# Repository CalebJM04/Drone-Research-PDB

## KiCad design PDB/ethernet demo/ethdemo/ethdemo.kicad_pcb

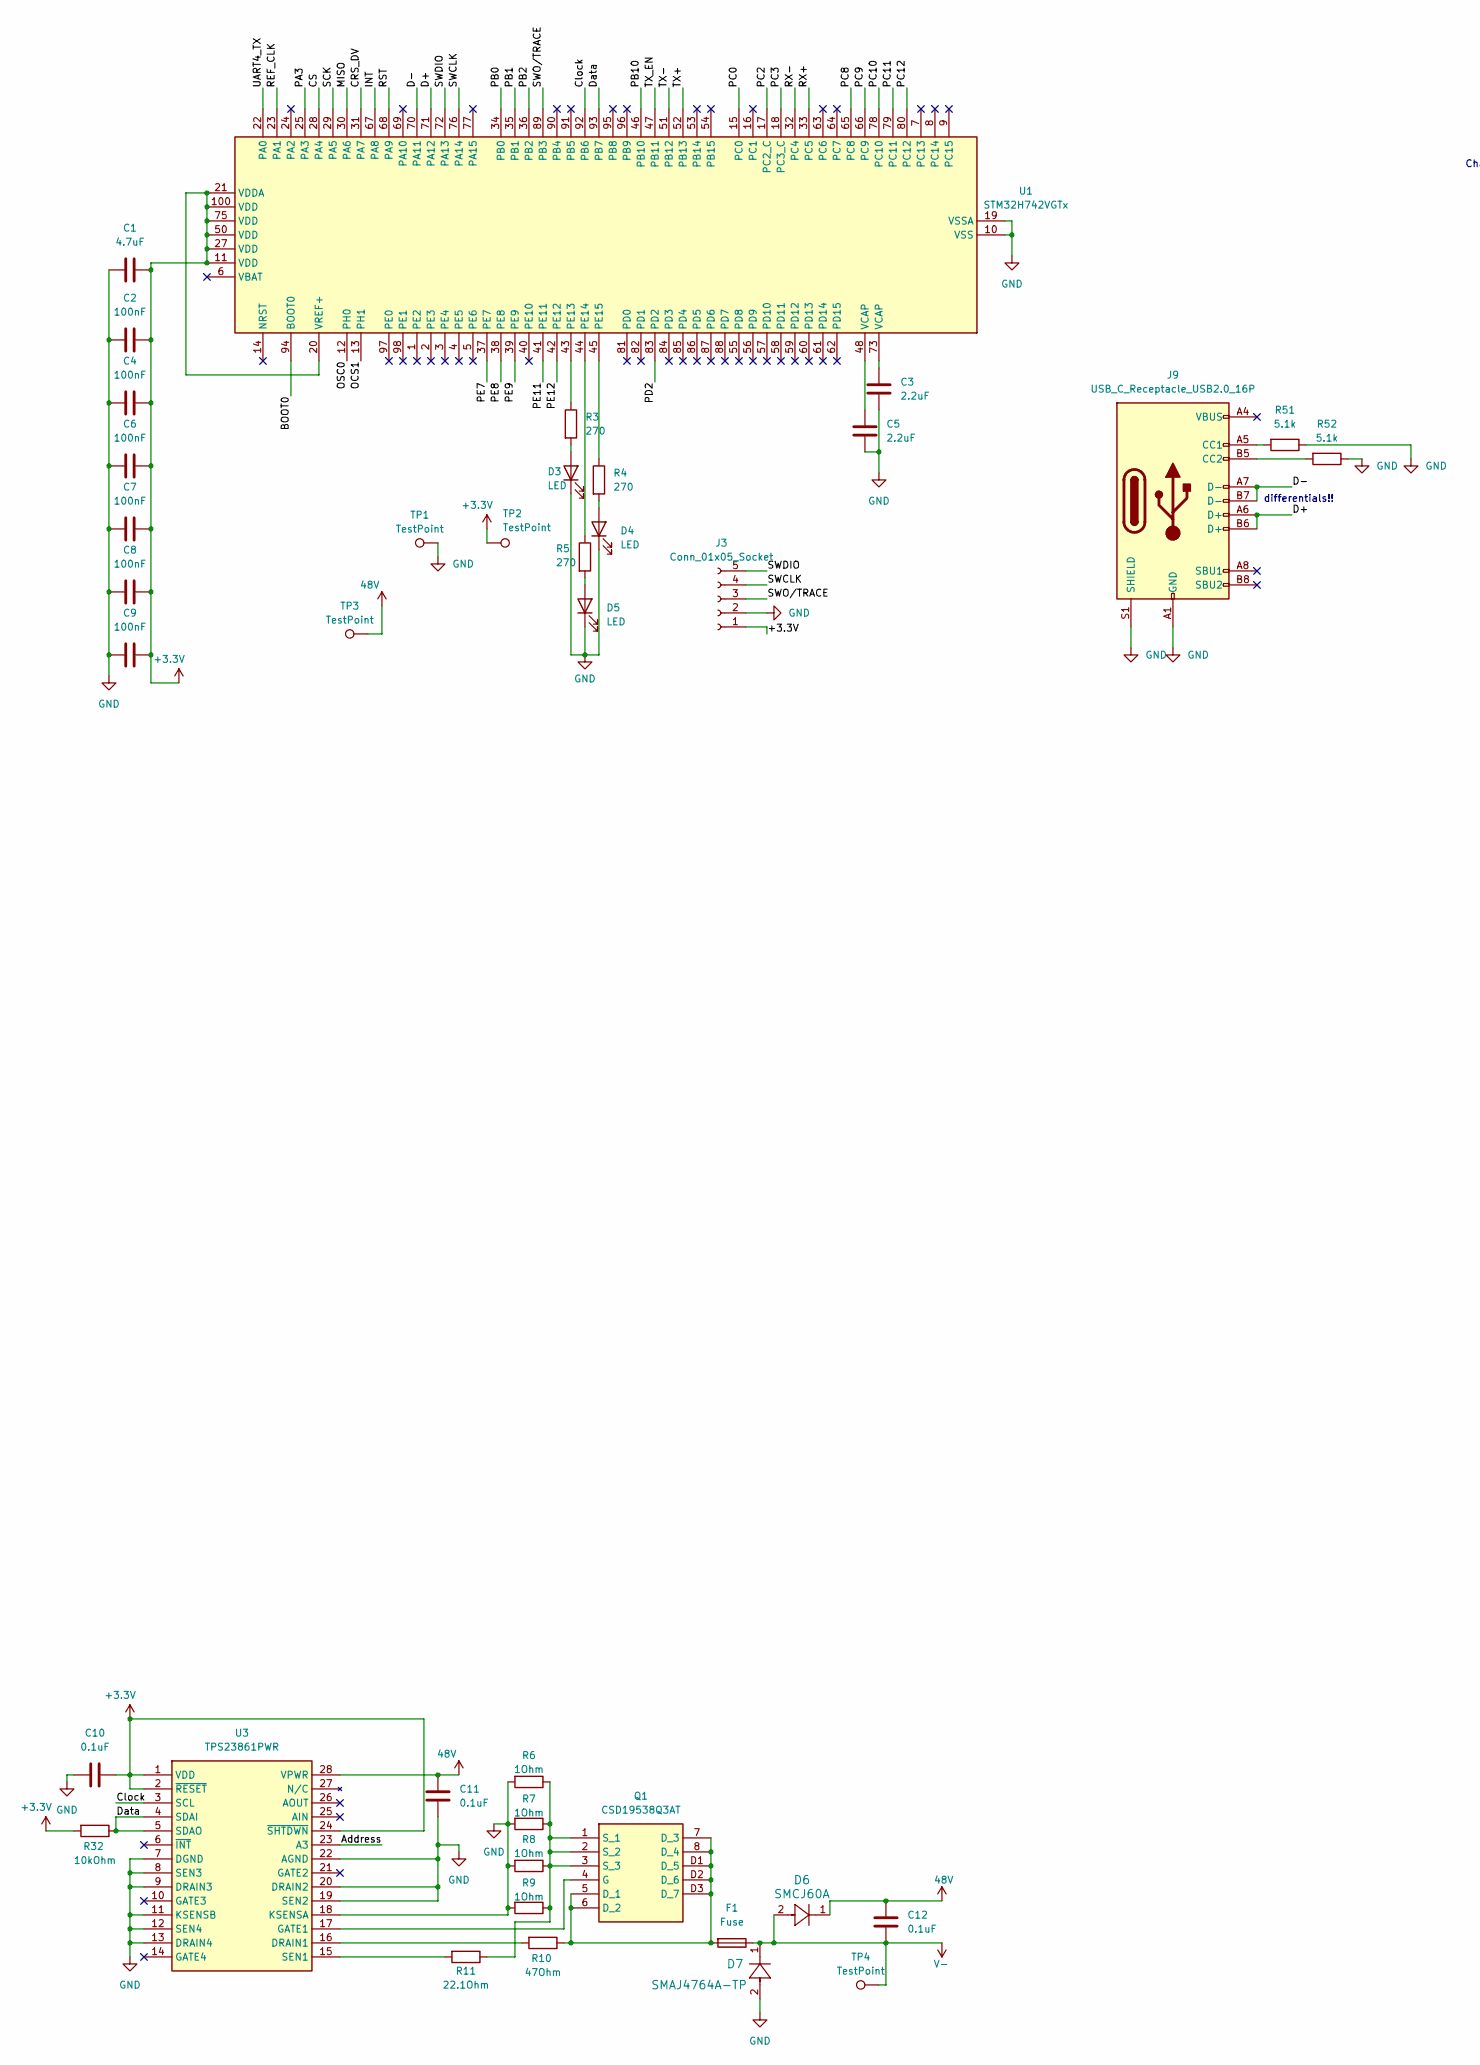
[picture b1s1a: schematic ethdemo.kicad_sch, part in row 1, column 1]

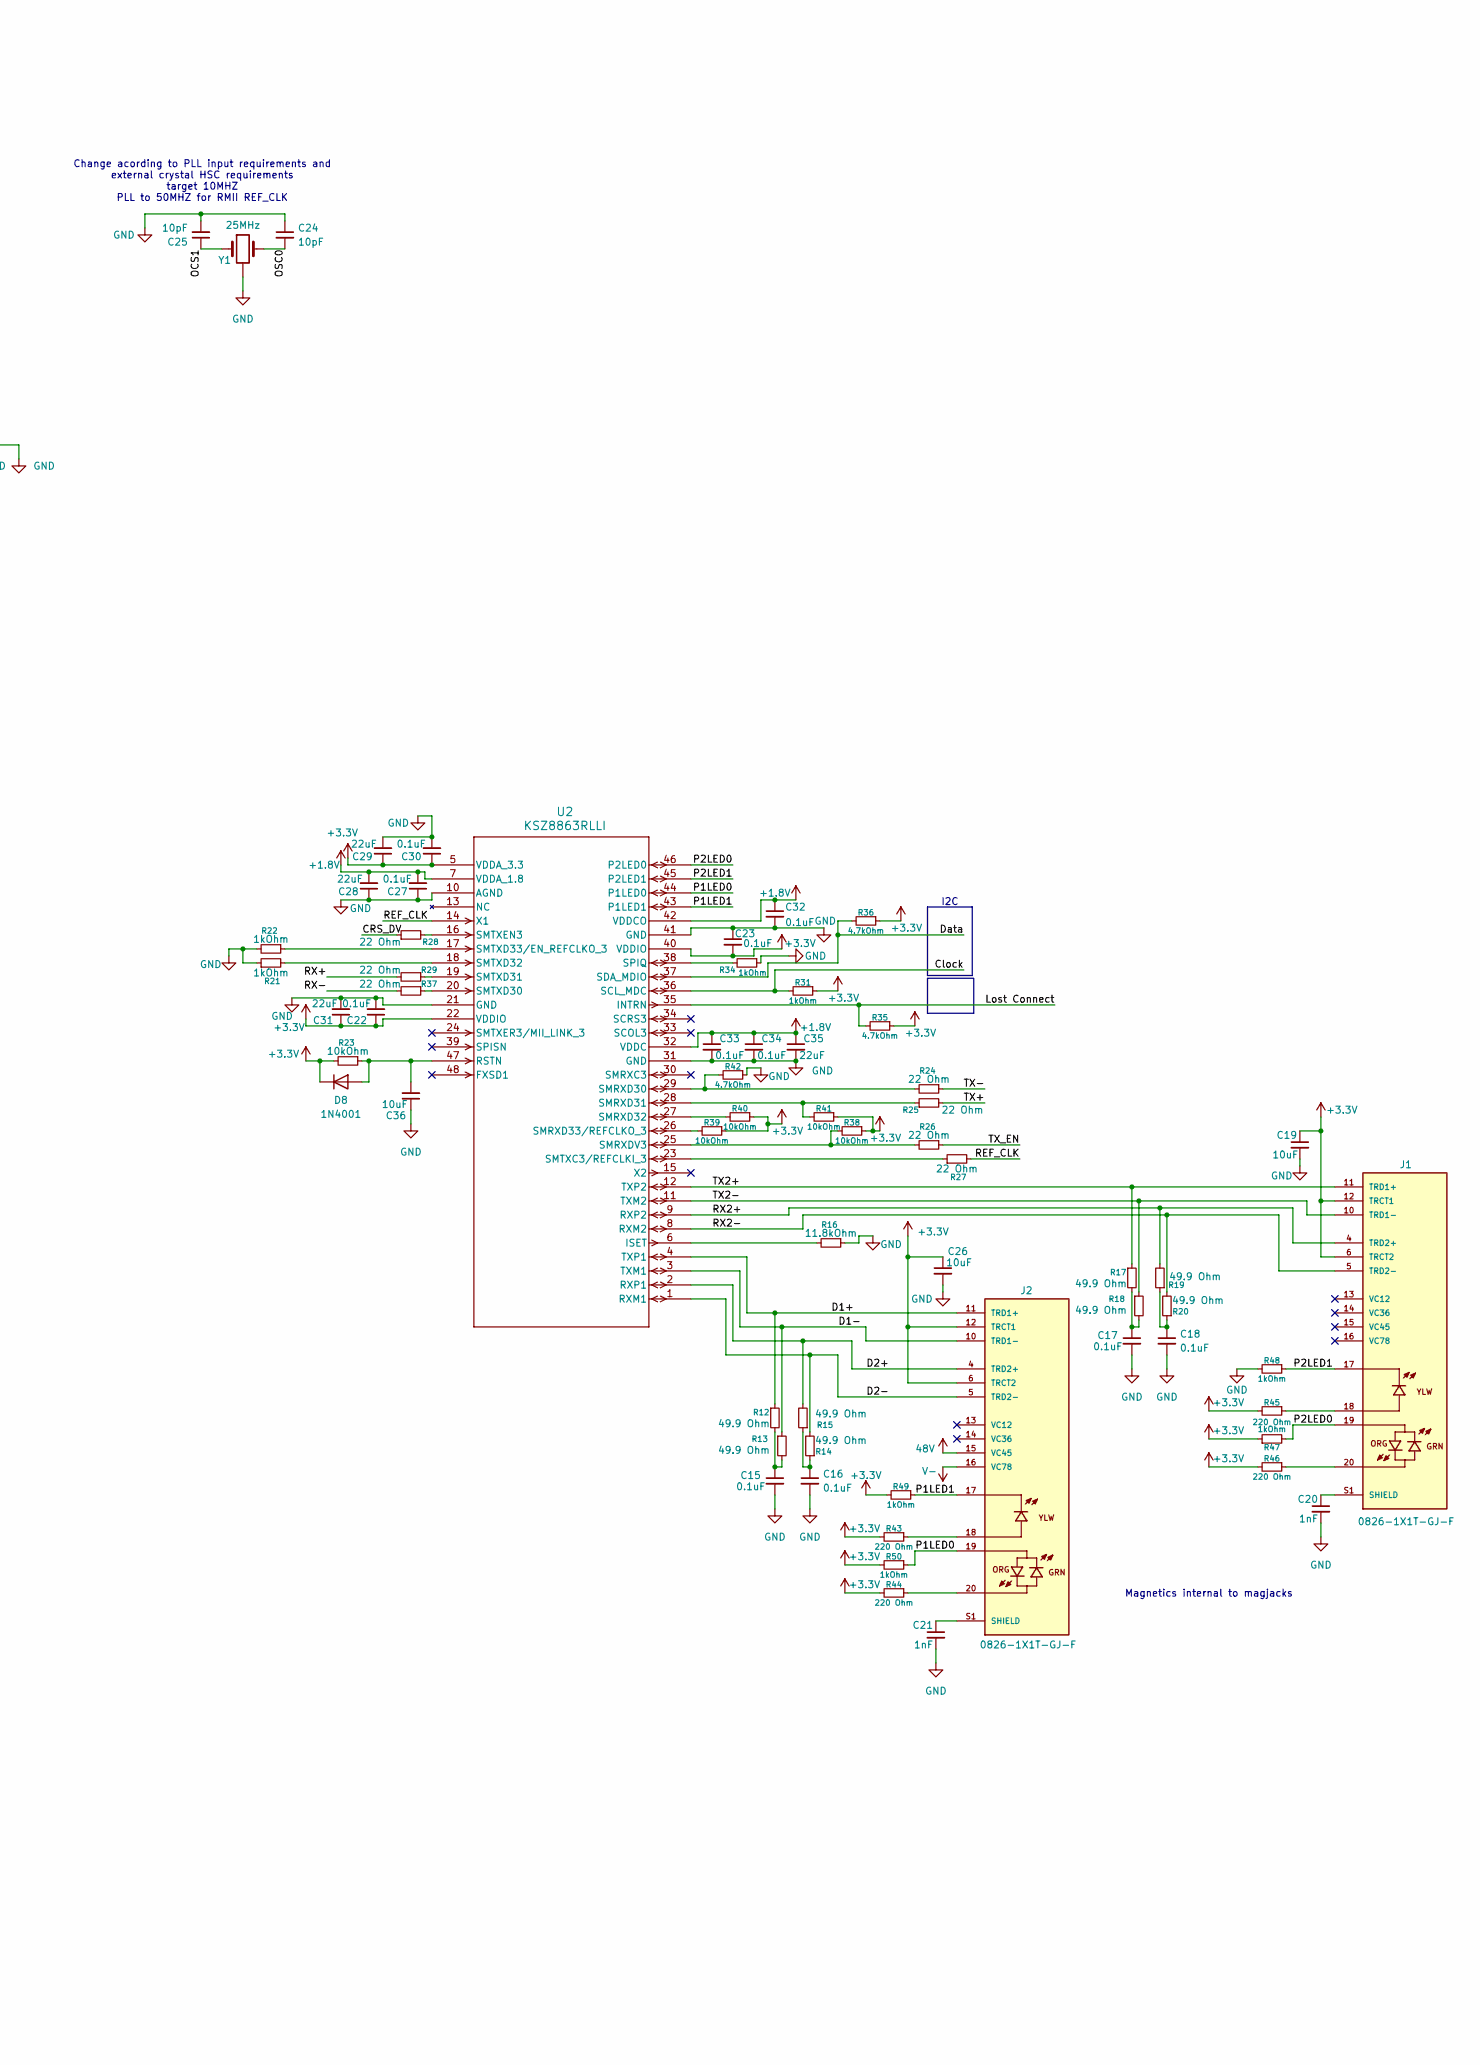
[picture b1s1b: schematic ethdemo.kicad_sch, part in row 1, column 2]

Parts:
C1: 4.7uF; C_0603_1608Metric
C2, C4, C6, C7, C8, C9: 100nF; C_0603_1608Metric
C3, C5: 2.2uF; C_0603_1608Metric
C10, C11, C12, C15, C16, C17, C18, C22, C23, C27, C30, C32, C33, C34: 0.1uF; C_0603_1608Metric
C19, C26, C36: 10uF; C_0603_1608Metric
C20, C21: 1nF; C_0603_1608Metric
C24, C25: 10pF; C_0603_1608Metric
C28, C29, C31, C35: 22uF; C_0603_1608Metric
D3, D4, D5: LED; LED_0805_2012Metric
D6: SMCJ60A
D7: SMAJ4764A-TP; SMAJ100CA_13_F
D8: 1N4001; D_SMA
F1: Fuse; Fuse_1206_3216Metric
J1, J2: 0826-1X1T-GJ-F; PARTREV D; DigiKey_Part_Number 5923-0826-1X1T-GJ-F-ND
J3: Conn_01x05_Socket; PinSocket_1x05_P2.54mm_Vertical
J9: USB_C_Receptacle_USB2.0_16P; USB_C_Receptacle_GCT_USB4105-xx-A_16P_TopMnt_Horizontal
Q1: CSD19538Q3AT; Mouser Part Number 595-CSD19538Q3AT
R3, R4, R5: 270; R_0603_1608Metric
R6, R7, R8, R9: 1Ohm; R_0603_1608Metric
R10: 47Ohm; R_0603_1608Metric
R11: 22.1Ohm; R_0603_1608Metric
R12, R13, R14, R15, R17, R18, R19, R20: 49.9 Ohm; R_0603_1608Metric
R16: 11.8kOhm; R_0603_1608Metric
R21, R22, R31, R34, R47, R48, R49, R50: 1kOhm; R_0603_1608Metric
R23, R32, R38, R39, R40, R41: 10kOhm; R_0603_1608Metric
R24, R25, R26, R27, R28, R29, R37: 22 Ohm; R_0603_1608Metric
R35, R36, R42: 4.7kOhm; R_0603_1608Metric
R43, R44, R45, R46: 220 Ohm; R_0603_1608Metric
R51, R52: 5.1k; R_0603_1608Metric_Pad0.98x0.95mm_HandSolder
TP1, TP2, TP3, TP4: TestPoint; TestPoint_Pad_D2.5mm
U1: STM32H742VGTx; LQFP-100_14x14mm_P0.5mm
U2: KSZ8863RLLI
U3: TPS23861PWR; Mouser Part Number 595-TPS23861PWR
Y1: 25MHz; Crystal_SMD_5032-4Pin_5.0x3.2mm

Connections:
48V: C11.2, C12.1, D6.1, J2.15 (VC45), TP3.1 (1_1), U3.28 (VPWR)
+1.8V: C27.2, C28.2, C32.1, C33.1, C34.1, C35.1, U2.7 (VDDA_1.8), U2.32 (VDDC), U2.42 (VDDCO)
+3.3V: C1.1, C2.1, C4.2, C6.1, C7.1, C8.1, C9.1, C10.1, C19.1, C22.1, C23.2, C26.1, C29.1, C30.1, C31.1, D8.1 (K), J1.6 (TRCT2), J1.12 (TRCT1), J2.6 (TRCT2), J2.12 (TRCT1), J3.1, R23.2, R31.1, R32.2, R35.1, R36.1, R38.1, R39.1, R40.1, R41.1, R43.2, R44.2, R45.2, R46.2, R47.1, R49.2, R50.2, TP2.1 (1_1), U1.11 (VDD), U1.20 (VREF+), U1.21 (VDDA), U1.27 (VDD), U1.50 (VDD), U1.75 (VDD), U1.100 (VDD), U2.5 (VDDA_3.3), U2.22 (VDDIO), U2.40 (VDDIO), U3.1 (VDD), U3.2 (~RESET), U3.24 (~SHTDWN)
/Address: U3.23 (A3)
/BOOT0: U1.94 (BOOT0)
/CRS_DV: R28.1, U1.31 (PA7)
/CS: U1.28 (PA4)
/Clock: R31.2, U1.92 (PB6), U2.36 (SCL_MDC), U3.3 (SCL)
/D1+: J2.11 (TRD1+), R12.1, U2.4 (TXP1)
/D1-: J2.10 (TRD1-), R13.1, U2.3 (TXM1)
/D2+: J2.4 (TRD2+), R15.2, U2.2 (RXP1)
/D2-: J2.5 (TRD2-), R14.2, U2.1 (RXM1)
/D+: J9.A6 (D+), J9.B6 (D+), U1.71 (PA12)
/D-: J9.A7 (D-), J9.B7 (D-), U1.70 (PA11)
/Data: R32.1, R36.2, U1.93 (PB7), U2.37 (SDA_MDIO), U3.4 (SDAI), U3.5 (SDAO)
/INT: U1.67 (PA8)
/Lost Connect: R35.2, U2.35 (INTRN)
/MISO: U1.30 (PA6)
/OCS1: C25.1, U1.13 (PH1), Y1.1
/OSC0: C24.2, U1.12 (PH0), Y1.3 (2)
/P1LED0: J2.19, R50.1, U2.44 (P1LED0)
/P1LED1: J2.17, R49.1, U2.43 (P1LED1)
/P2LED0: J1.19, R47.2, U2.46 (P2LED0)
/P2LED1: J1.17, R48.1, U2.45 (P2LED1)
/PA3: U1.25 (PA3)
/PB0: U1.34 (PB0)
/PB1: U1.35 (PB1)
/PB2: U1.36 (PB2)
/PB10: U1.46 (PB10)
/PC0: U1.15 (PC0)
/PC2: U1.17 (PC2_C)
/PC3: U1.18 (PC3_C)
/PC8: U1.65 (PC8)
/PC9: U1.66 (PC9)
/PC10: U1.78 (PC10)
/PC11: U1.79 (PC11)
/PC12: U1.80 (PC12)
/PD2: U1.83 (PD2)
/PE7: U1.37 (PE7)
/PE8: U1.38 (PE8)
/PE9: U1.39 (PE9)
/PE11: U1.41 (PE11)
/PE12: U1.42 (PE12)
/REF_CLK: R27.2, U1.23 (PA1), U2.14 (X1)
/RST: U1.68 (PA9)
/RX2+: J1.4 (TRD2+), R19.2, U2.9 (RXP2)
/RX2-: J1.5 (TRD2-), R20.2, U2.8 (RXM2)
/RX+: R29.2, U1.33 (PC5)
/RX-: R37.2, U1.32 (PC4)
/SCK: U1.29 (PA5)
/SWCLK: J3.4, U1.76 (PA14)
/SWDIO: J3.5, U1.72 (PA13)
/SWO/TRACE: J3.3, U1.89 (PB3)
/TX2+: J1.11 (TRD1+), R17.1, U2.12 (TXP2)
/TX2-: J1.10 (TRD1-), R18.1, U2.11 (TXM2)
/TX+: R25.2, U1.52 (PB13)
/TX-: R24.1, U1.51 (PB12)
/TX_EN: R26.1, U1.47 (PB11)
/UART4_TX: U1.22 (PA0)
GND: C1.2, C2.2, C3.1, C4.1, C5.1, C6.2, C7.2, C8.2, C9.2, C10.2, C11.1, C15.2, C16.2, C17.2, C18.2, C19.2, C20.2, C21.2, C22.2, C23.1, C24.1, C25.2, C26.2, C27.1, C28.1, C29.2, C30.2, C31.2, C32.2, C33.2, C34.2, C35.2, C36.1, D3.1 (K), D4.1 (K), D5.1 (K), D7.2, J3.2, J9.A1 (GND), J9.A12 (GND), J9.B1 (GND), J9.B12 (GND), J9.S1 (SHIELD), R6.2, R7.2, R8.2, R9.2, R16.1, R21.1, R22.2, R34.1, R42.1, R48.2, R51.1, R52.1, TP1.1 (1_1), U1.10 (VSS), U1.19 (VSSA), U1.26 (VSS), U1.49 (VSS), U1.74 (VSS), U1.99 (VSS), U2.10 (AGND), U2.21 (GND), U2.31 (GND), U2.41 (GND), U3.7 (DGND), U3.8 (SEN3), U3.9 (DRAIN3), U3.11 (KSENSB), U3.12 (SEN4), U3.13 (DRAIN4), U3.18 (KSENSA), U3.19 (SEN2), U3.20 (DRAIN2), U3.22 (AGND), Y1.2 (GND)
unnamed: C3.2, U1.73 (VCAP)
unnamed: C5.2, U1.48 (VCAP)
unnamed: C15.1, R12.2, R13.2
unnamed: C16.1, R14.1, R15.1
unnamed: C17.1, R17.2, R18.2
unnamed: C18.1, R19.1, R20.1
unnamed: C20.1, J1.S1 (SHIELD), J1.S2 (SHIELD)
unnamed: C21.1, J2.S1 (SHIELD), J2.S2 (SHIELD)
unnamed: D3.2 (A), R3.2
unnamed: D4.2 (A), R4.2
unnamed: D5.2 (A), R5.2
unnamed: C36.2, D8.2 (A), R23.1, U2.47 (RSTN)
unnamed: J1.18, R45.1
unnamed: J1.20, R46.1
unnamed: J2.18, R43.1
unnamed: J2.20, R44.1
unnamed: J9.A5 (CC1), R51.2
unnamed: J9.B5 (CC2), R52.2
unnamed: F1.2, Q1.5 (D_1), Q1.6 (D_2), Q1.7 (D_3), Q1.8 (D_4), Q1.D1 (D_5), Q1.D2 (D_6), Q1.D3 (D_7), R10.1
unnamed: Q1.4 (G), U3.17 (GATE1)
unnamed: Q1.1 (S_1), Q1.2 (S_2), Q1.3 (S_3), R6.1, R7.1, R8.1, R9.1, R11.1
unnamed: R3.1, U1.43 (PE13)
unnamed: R5.1, U1.44 (PE14)
unnamed: R4.1, U1.45 (PE15)
unnamed: R16.2, U2.6 (ISET)
unnamed: R24.2, R42.2, U2.29 (SMRXD30)
unnamed: R25.1, R41.2, U2.28 (SMRXD31)
unnamed: R40.2, U2.27 (SMRXD32)
unnamed: R39.2, U2.26 (SMRXD33/REFCLKO_3)
unnamed: R26.2, R38.2, U2.25 (SMRXDV3)
unnamed: R27.1, U2.23 (SMTXC3/REFCLKI_3)
unnamed: R37.1, U2.20 (SMTXD30)
unnamed: R29.1, U2.19 (SMTXD31)
unnamed: R21.2, U2.18 (SMTXD32)
unnamed: R22.1, U2.17 (SMTXD33/EN_REFCLKO_3)
unnamed: R28.2, U2.16 (SMTXEN3)
unnamed: R34.2, U2.38 (SPIQ)
unnamed: R10.2, U3.16 (DRAIN1)
unnamed: R11.2, U3.15 (SEN1)
V-: C12.2, D6.2, D7.1, F1.1, J2.16 (VC78), TP4.1 (1_1)

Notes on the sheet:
Magnetics internal to magjacks
differentials!!
I2C
Change acording to PLL input requirements and external crystal HSC requirements target 10MHZ PLL to 50MHZ for RMII REF_CLK

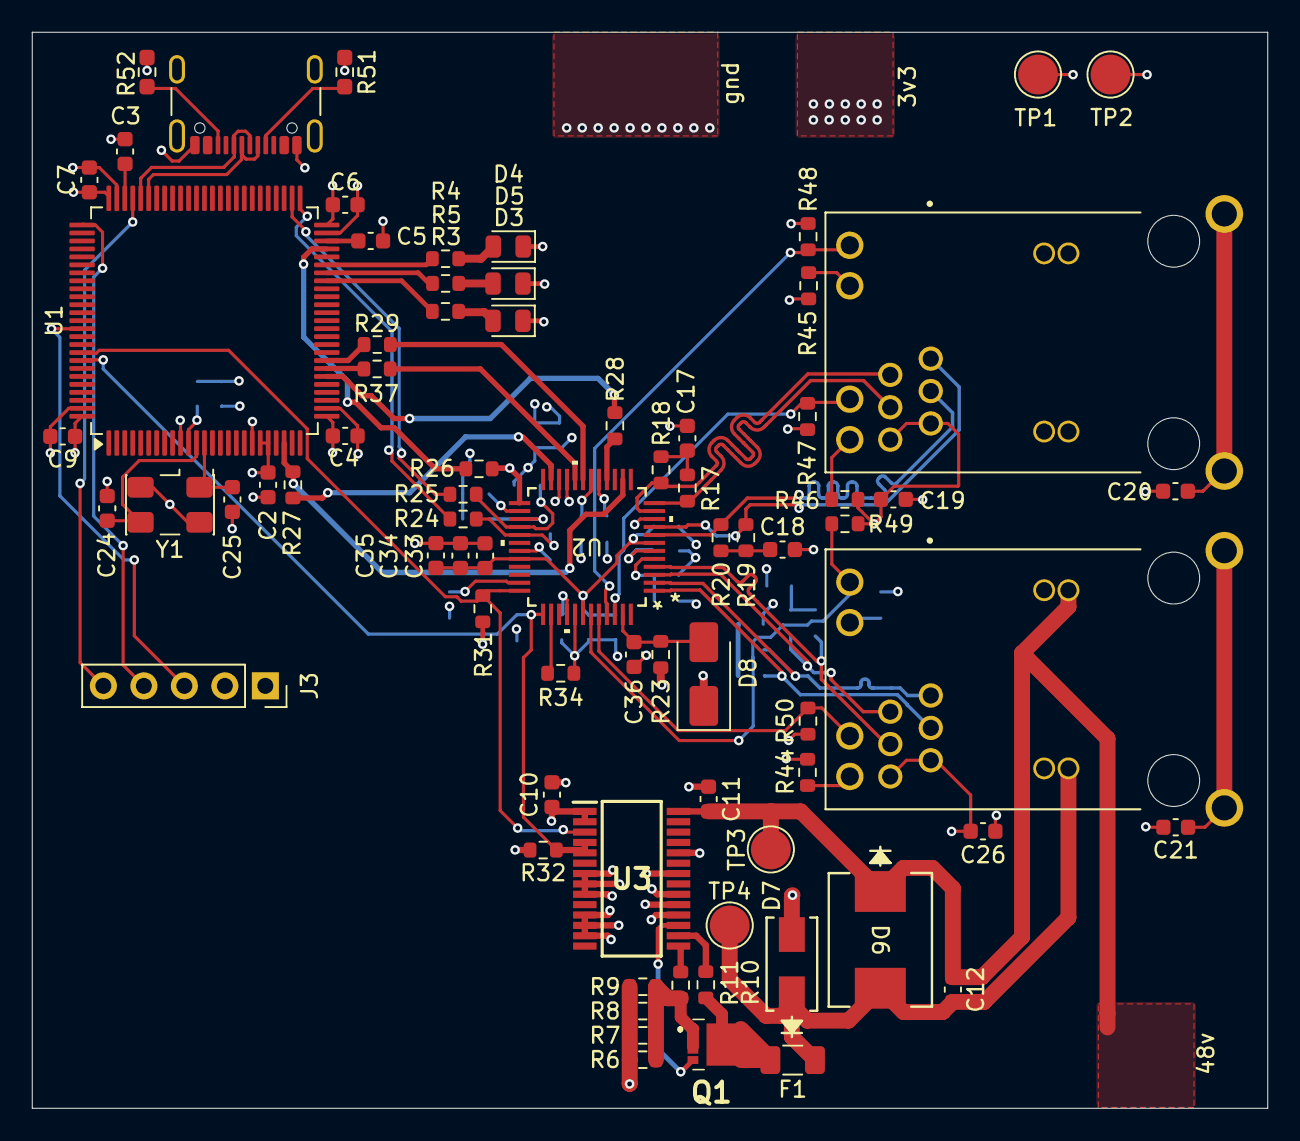
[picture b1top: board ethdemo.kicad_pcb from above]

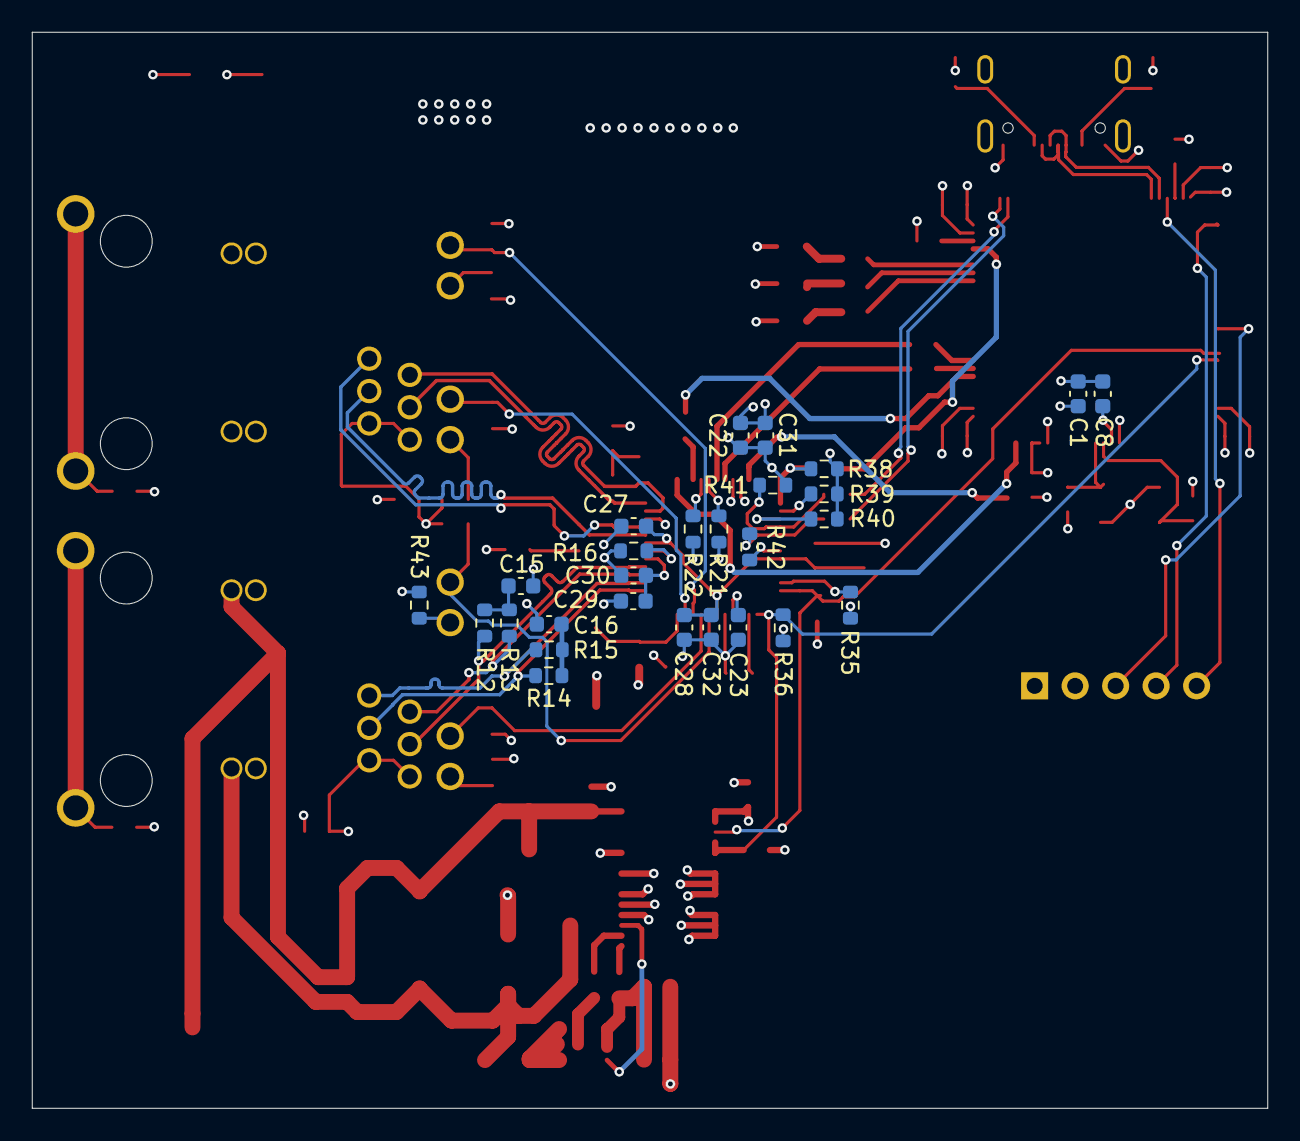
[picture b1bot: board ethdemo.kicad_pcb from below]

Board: 4 copper layers, 77.5 x 67.5 mm, 102 parts (27 on the bottom side), 73 nets.

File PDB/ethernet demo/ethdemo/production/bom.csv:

Designator,Footprint,Quantity,Value,Digykey Part #,Mouser Part#,Mfr Part#
C1,0603,1,4.7uF,1276-1044-6-ND,,CL10A475KP8NNNC
"C10, C11, C12, C15, C16, C17, C18, C22, C23, C27, C30, C32, C33, C34",0603,14,0.1uF,1276-6807-2-ND,,CL10B104KC8NNNC
"C19, C26, C36",0603,3,10uF,1276-1869-2-ND,,CL10A106MA8NRNC
"C2, C4, C6, C7, C8, C9",0603,6,100nF,1276-1869-2-ND,,CL10A106MA8NRNC
"C20, C21",0603,2,1nF,1276-CL10B102KC8NNNDDKR-ND,,CL10B102KC8NNND
"C24, C25",0603,2,10pF,1276-6588-1-ND,,CL10C100JC81PNC
"C28, C29, C31, C35",0603,4,22uF,1276-1023-6-ND,,CL10C220JB8NNNC
"C3, C5",0603,2,2.2uF,1276-1085-2-ND,,CL10A225KP8NNNC
"D3, D4, D5",0805,3,LED,160-1426-2-ND,,LTST-C171KGKT
D6,SMCJ60A,1,SMCJ60A,SMCJ60ABTR-ND,,SMCJ60A
D7,SMAJ100CA_13_F,1,SMAJ4764A-TP,SMAJ4764A-TPMSTR-ND,,SMAJ4764A-TP
D8,D_SMA,1,1N4001,5272-1N4001WTR-ND,,1N4001W
F1,1206,1,Fuse,F8130TR-ND,576-1206L010/60WR ,1206L010/60WR 
"J1, J2",0826-1X1T-GJ-F,2,0826-1X1T-GJ-F,5923-0826-1X1T-GJ-F-ND,,0826-1X1T-GJ-F
J3,PinSocket_1x05_P2.54mm_Vertical,1,Conn_01x05_Socket,,,no part
J9,USB_C_Receptacle_GCT_USB4105-xx-A_16P_TopMnt_Horizontal,1,USB_C_Receptacle_USB2.0_16P,2073-USB4085-GF-ATR-ND,,USB4085-GF-A
Q1,CSD19538Q3AT,1,CSD19538Q3AT,296-44352-2-ND,,CSD19538Q3A
R10,0603,1,47Ohm,1712-TLMQ1JER047FTDTR-ND,,TLMQ1JER047FTD
R11,0603,1,22.1Ohm,541-RCS060322R1FKEATR-ND,,RCS060322R1FKEA
"R12, R13, R14, R15, R17, R18, R19, R20",0603,8,49.9 Ohm,541-2784-2-ND,,RCS060349R9FKEA
R16,0603,1,11.8kOhm,541-RCS060311K8FKEATR-ND,,RCS060311K8FKEA
"R21, R22, R31, R34, R47, R48, R49, R50",0603,8,1kOhm,541-RCP0603W1K00FEATR-ND,,RCP0603W1K00FEA
"R23, R32, R38, R39, R40, R41",0603,6,10kOhm,541-2795-2-ND,,RCS060310K0FKEA
"R24, R25, R26, R27, R28, R29, R37",0603,7,22 Ohm,541-10442-2-ND,,RCS060322R0FKEA
"R3, R4, R5",0603,3,270 Ohm,541-10445-2-ND,,RCS0603270RFKEA
"R35, R36, R42",0603,3,4.7kOhm,2019-SG73P1JTTD4701FTR-ND,,SG73P1JTTD4701F
"R43, R44, R45, R46",0603,4,220 Ohm,2019-SG73P1JTTD2200FTR-ND,,SG73P1JTTD2200F
"R51, R52",0603,2,5.1kOhm,541-10481-2-ND,,RCS06035K10FKEA
"R6, R7, R8, R9",0603,4,1Ohm,2019-SG73P1JTTD1R00FTR-ND,,SG73P1JTTD1R00F
"TP1, TP2, TP3, TP4",TestPoint_Pad_D2.5mm,4,TestPoint,,,no part
U1,LQFP-100_14x14mm_P0.5mm,1,STM32H742VGTx,497-STM32H742VGT6-ND,511-STM32H742VGT6,STM32H742VGT6
U2,KSZ8863RLLI,1,KSZ8863RLLI,576-3752-ND,998-KSZ8863RLLI,KSZ8863RLLI
U3,TPS23861PWR,1,TPS23861PWR,296-TPS23861PWRTR-ND,595-TPS23861PWR,TPS23861PWR
Y1,Crystal_SMD_5032-4Pin_5.0x3.2mm,1,25MHz,XC2698TR-ND,520-250-10-30B-CKMT,ECS-250-10-30B-CKM-TR

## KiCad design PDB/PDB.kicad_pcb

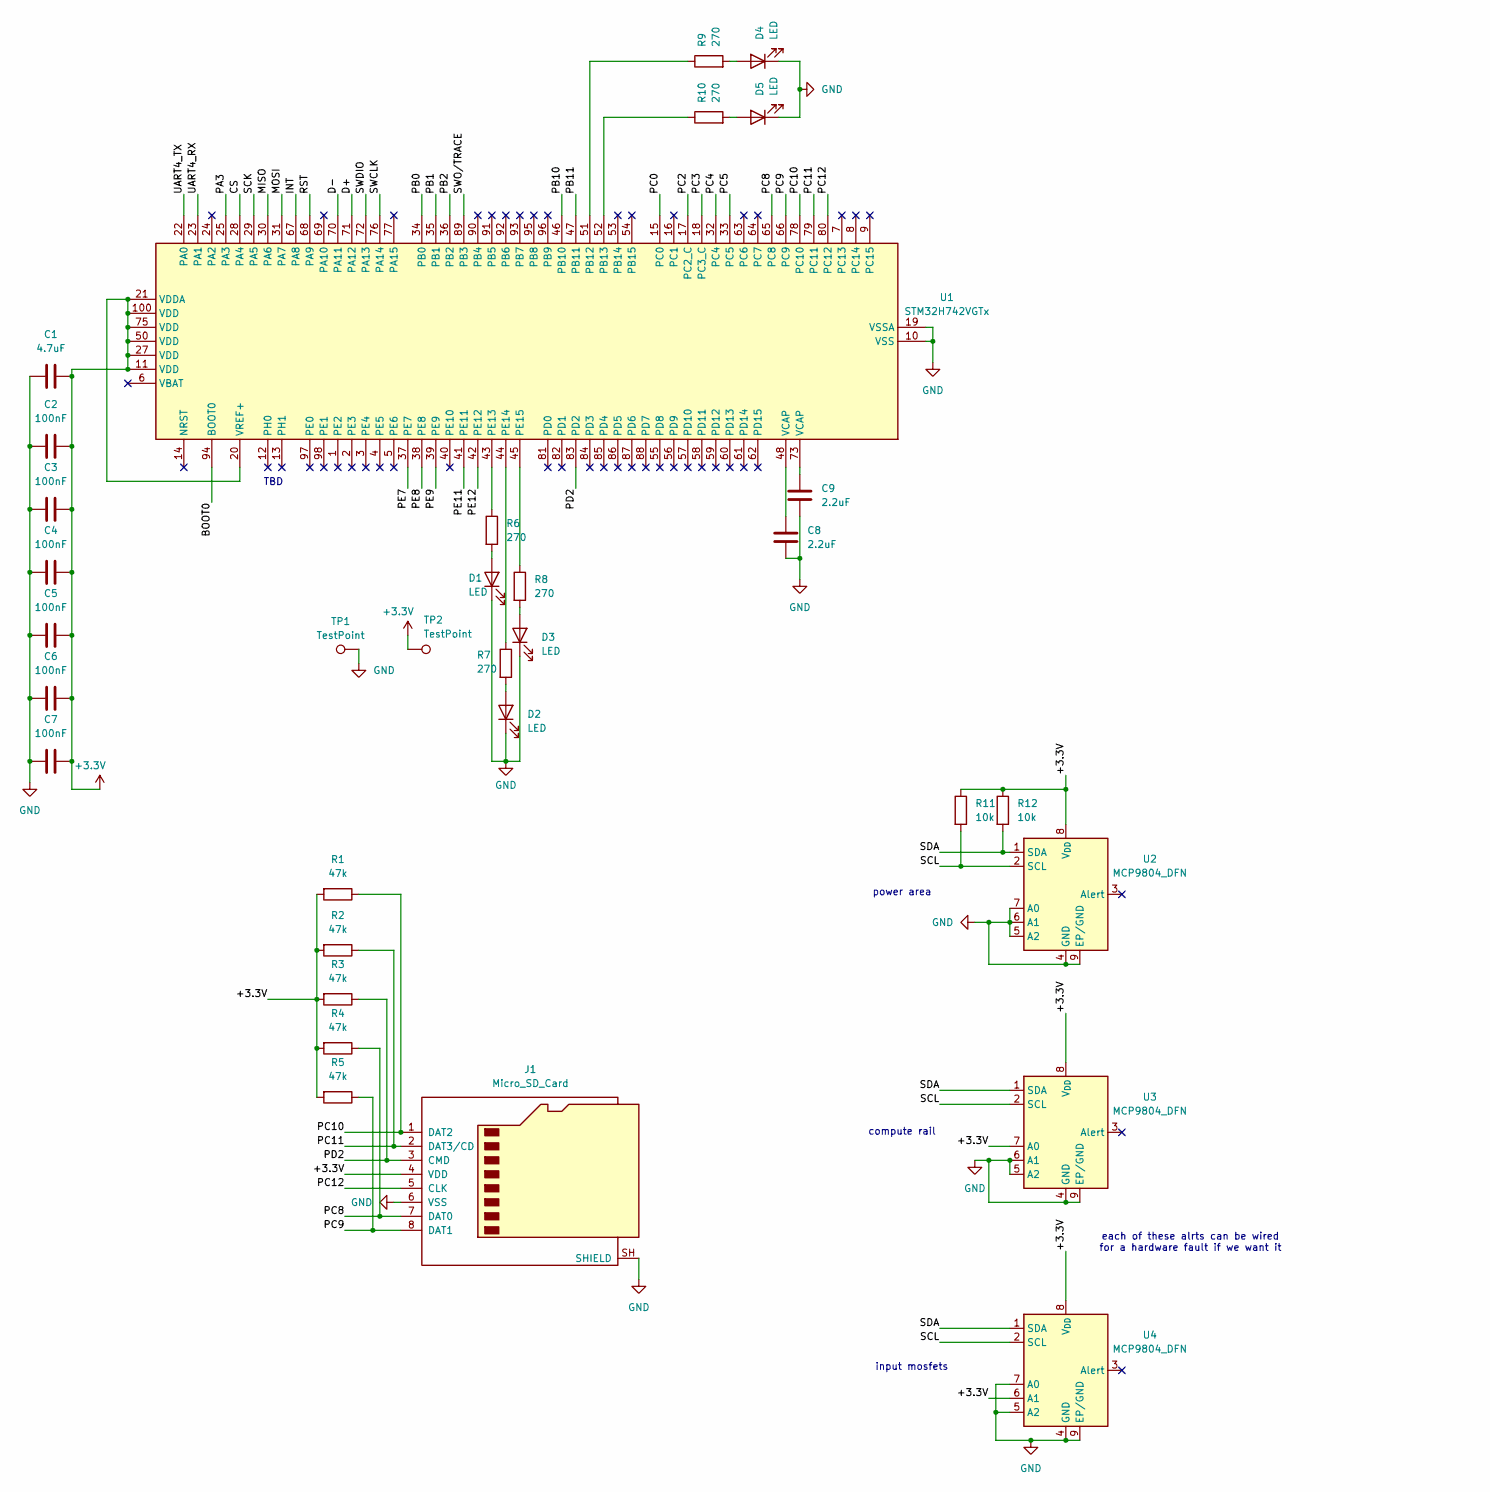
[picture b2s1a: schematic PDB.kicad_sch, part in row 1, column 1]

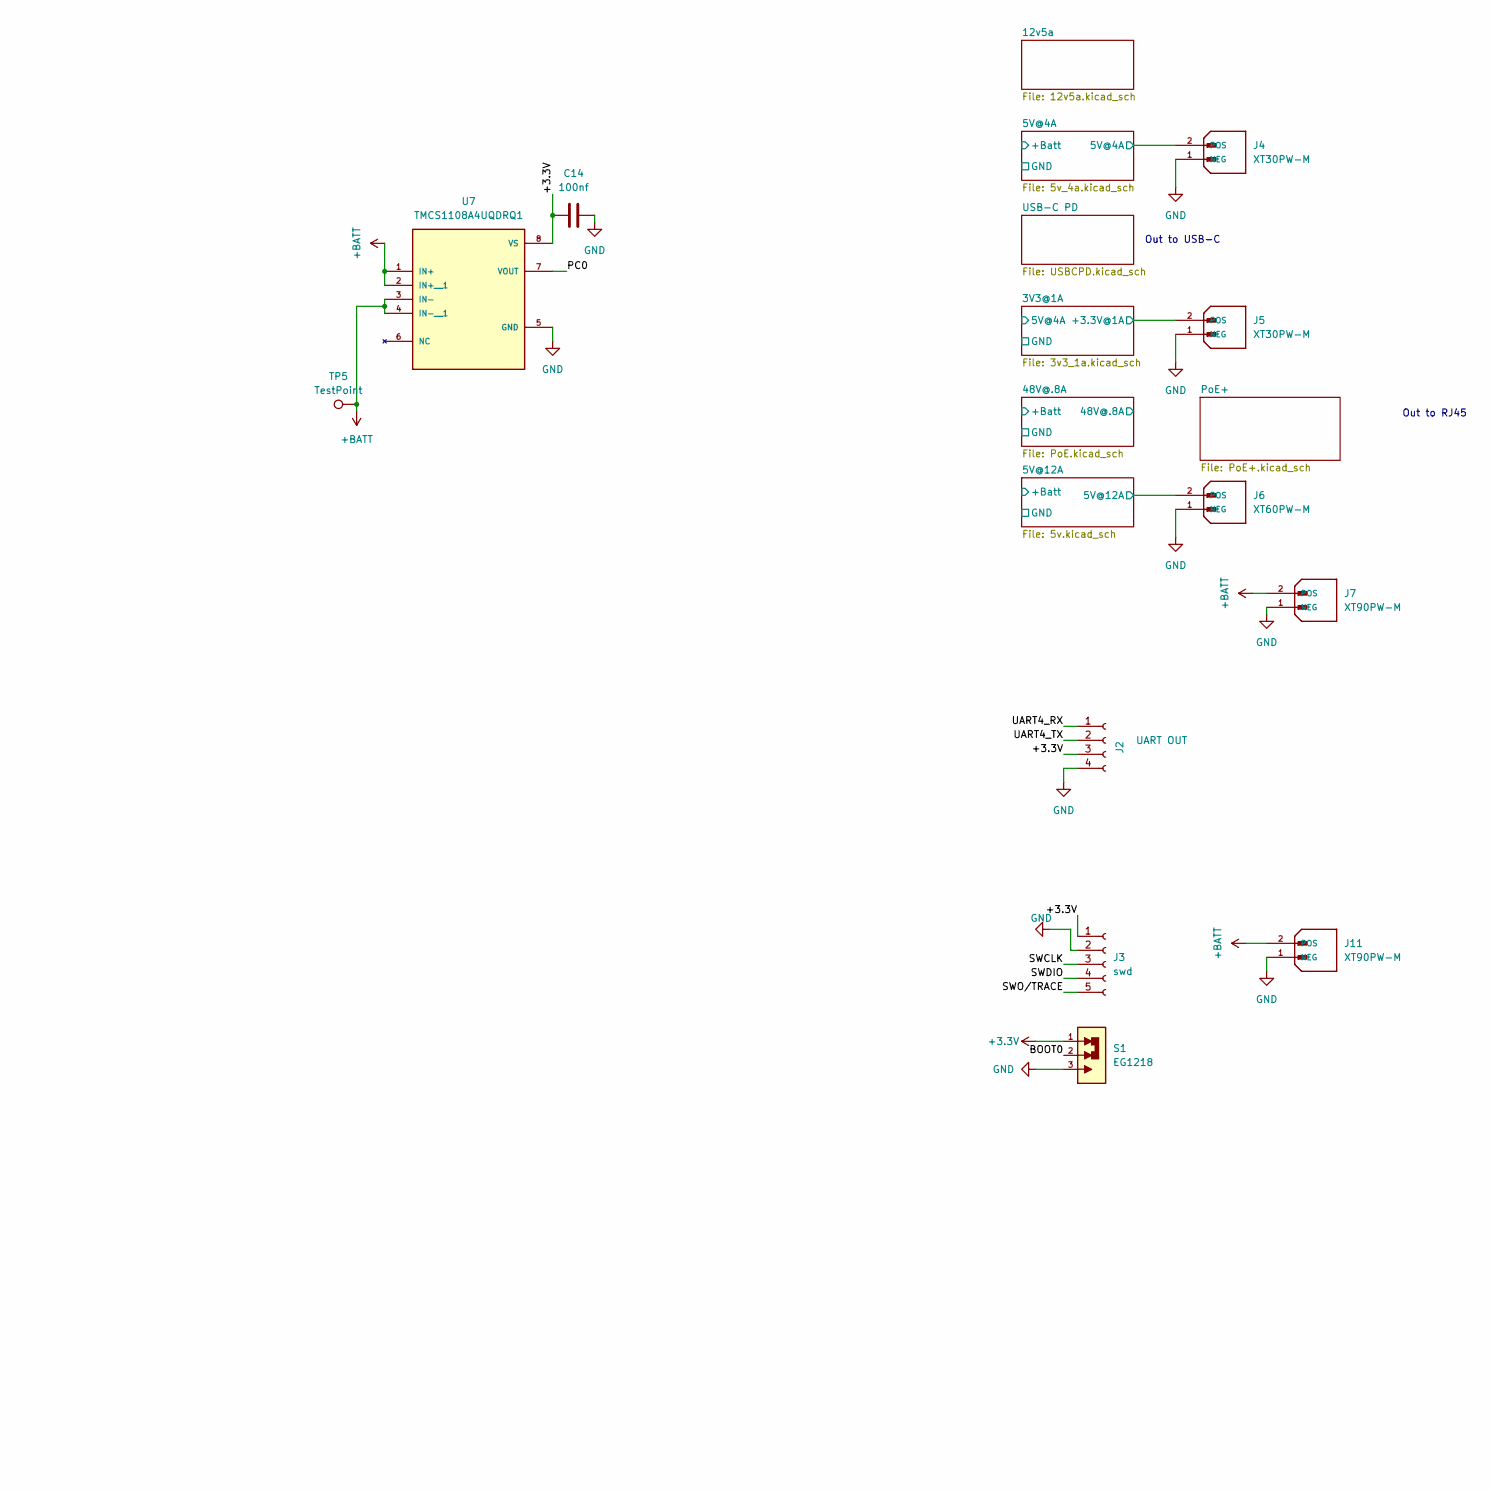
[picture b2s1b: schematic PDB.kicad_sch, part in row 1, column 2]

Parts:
C1: 4.7uF; C_0603_1608Metric
C2, C3, C4, C5, C6, C7: 100nF; C_0603_1608Metric
C8, C9: 2.2uF; C_0603_1608Metric
C14: 100nf; C_0603_1608Metric
D1, D2, D3, D4, D5: LED; LED_0805_2012Metric
J1: Micro_SD_Card; microSD_HC_Hirose_DM3AT-SF-PEJM5
J2: UART OUT; PinHeader_1x04_P2.54mm_Vertical
J3: swd; PinHeader_1x05_P2.54mm_Vertical
J4, J5: XT30PW-M; AMASS_XT90PW-M; PARTREV V00
J6: XT60PW-M; AMASS_XT90PW-M; PARTREV V00
J7, J11: XT90PW-M; AMASS_XT90PW-M; PARTREV V00
R1, R2, R3, R4, R5: 47k; R_0603_1608Metric
R6, R7, R8, R9, R10: 270; R_0603_1608Metric
R11, R12: 10k; R_0603_1608Metric_Pad0.98x0.95mm_HandSolder
S1: EG1218; SW_EG1218
TP1, TP2: TestPoint; TestPoint_Pad_D2.5mm
TP5: TestPoint; TestPoint_Pad_D2.0mm
U1: STM32H742VGTx; LQFP-100_14x14mm_P0.5mm
U2, U3, U4: MCP9804_DFN; DFN-8-1EP_3x2mm_P0.5mm_EP1.7x1.4mm
U7: TMCS1108A4UQDRQ1; SOIC127P599X175-8N; PARTREV July 2021

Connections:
5V@12A: J6.2 (POS); also elsewhere on the board
+3.3V: C1.1, C2.1, C3.2, C4.1, C5.1, C6.1, C7.1, C14.1, J1.4 (VDD), J2.3, J3.1, J5.2 (POS), R1.2, R2.2, R3.2, R4.2, R5.2, R11.1, R12.1, S1.1, TP2.1 (1_1), U1.11 (VDD), U1.20 (VREF+), U1.21 (VDDA), U1.27 (VDD), U1.50 (VDD), U1.75 (VDD), U1.100 (VDD), U2.8 (V_{DD}), U3.7 (A0), U3.8 (V_{DD}), U4.6 (A1), U4.8 (V_{DD}), U7.8 (VS); also elsewhere on the board
+5V@4A: J4.2 (POS); also elsewhere on the board
+BATT: J7.2 (POS), J11.2 (POS), TP5.1 (1_1), U7.1 (IN+), U7.2 (IN+__1), U7.3 (IN-), U7.4 (IN-__1); also elsewhere on the board
/BOOT0: S1.2, U1.94 (BOOT0)
/CS: U1.28 (PA4)
/D+: U1.71 (PA12)
/D-: U1.70 (PA11)
/INT: U1.67 (PA8)
/MISO: U1.30 (PA6)
/MOSI: U1.31 (PA7)
/PA3: U1.25 (PA3)
/PB0: U1.34 (PB0)
/PB1: U1.35 (PB1)
/PB2: U1.36 (PB2)
/PB10: U1.46 (PB10)
/PB11: U1.47 (PB11)
/PC0: U1.15 (PC0), U7.7 (VOUT)
/PC2: U1.17 (PC2_C)
/PC3: U1.18 (PC3_C)
/PC4: U1.32 (PC4)
/PC5: U1.33 (PC5)
/PC8: J1.7 (DAT0), R4.1, U1.65 (PC8)
/PC9: J1.8 (DAT1), R5.1, U1.66 (PC9)
/PC10: J1.1 (DAT2), R1.1, U1.78 (PC10)
/PC11: J1.2 (DAT3/CD), R2.1, U1.79 (PC11)
/PC12: J1.5 (CLK), U1.80 (PC12)
/PD2: J1.3 (CMD), R3.1, U1.83 (PD2)
/PE7: U1.37 (PE7)
/PE8: U1.38 (PE8)
/PE9: U1.39 (PE9)
/PE11: U1.41 (PE11)
/PE12: U1.42 (PE12)
/RST: U1.68 (PA9)
/SCK: U1.29 (PA5)
/SCL: R11.2, U2.2 (SCL), U3.2 (SCL), U4.2 (SCL)
/SDA: R12.2, U2.1 (SDA), U3.1 (SDA), U4.1 (SDA)
/SWCLK: J3.3, U1.76 (PA14)
/SWDIO: J3.4, U1.72 (PA13)
/SWO/TRACE: J3.5, U1.89 (PB3)
/UART4_RX: J2.1, U1.23 (PA1)
/UART4_TX: J2.2, U1.22 (PA0)
GND: C1.2, C2.2, C3.1, C4.2, C5.2, C6.2, C7.2, C8.1, C9.1, C14.2, D1.1 (K), D2.1 (K), D3.1 (K), D4.1 (K), D5.1 (K), J1.6 (VSS), J1.SH (SHIELD), J2.4, J3.2, J4.1 (NEG), J5.1 (NEG), J6.1 (NEG), J7.1 (NEG), J11.1 (NEG), S1.3, TP1.1 (1_1), U1.10 (VSS), U1.19 (VSSA), U1.26 (VSS), U1.49 (VSS), U1.74 (VSS), U1.99 (VSS), U2.4 (GND), U2.5 (A2), U2.6 (A1), U2.7 (A0), U2.9 (EP/GND), U3.4 (GND), U3.5 (A2), U3.6 (A1), U3.9 (EP/GND), U4.4 (GND), U4.5 (A2), U4.7 (A0), U4.9 (EP/GND), U7.5 (GND); also elsewhere on the board
unnamed: C8.2, U1.48 (VCAP)
unnamed: C9.2, U1.73 (VCAP)
unnamed: D1.2 (A), R6.2
unnamed: D2.2 (A), R7.2
unnamed: D3.2 (A), R8.2
unnamed: D4.2 (A), R9.2
unnamed: D5.2 (A), R10.2
unnamed: R9.1, U1.51 (PB12)
unnamed: R10.1, U1.52 (PB13)
unnamed: R6.1, U1.43 (PE13)
unnamed: R7.1, U1.44 (PE14)
unnamed: R8.1, U1.45 (PE15)

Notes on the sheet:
power area
TBD
compute rail
input mosfets
Out to RJ45
each of these alrts can be wired for a hardware fault if we want it
Out to USB-C

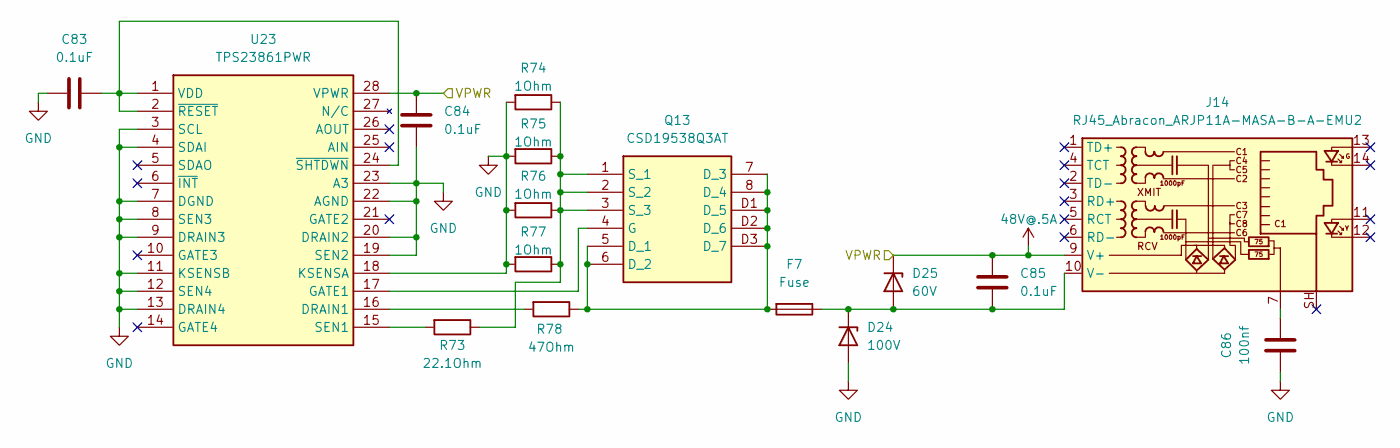
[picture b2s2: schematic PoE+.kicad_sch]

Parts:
C83, C84: 0.1uF; C_0603_1608Metric
C85: 0.1uF
C86: 100nf; C_0603_1608Metric
D24: 100V
D25: 60V
F7: Fuse; Fuse_1206_3216Metric
J14: RJ45_Abracon_ARJP11A-MASA-B-A-EMU2; RJ45_Abracon_ARJP11A-MA_Horizontal
Q13: CSD19538Q3AT; Mouser Part Number 595-CSD19538Q3AT
R73: 22.1Ohm; R_0603_1608Metric
R74, R75, R76, R77: 1Ohm; R_0603_1608Metric
R78: 47Ohm; R_0603_1608Metric
U23: TPS23861PWR; SOP65P640X120-28N; Mouser Part Number 595-TPS23861PWR

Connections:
48V@.5A: C84.2, C85.1, D25.1 (K), J14.9 (V+), U23.28 (VPWR)
GND: C83.2, C84.1, C86.1, D24.2 (A), R74.2, R75.2, R76.2, R77.2, U23.3 (SCL), U23.4 (SDAI), U23.7 (DGND), U23.8 (SEN3), U23.9 (DRAIN3), U23.11 (KSENSB), U23.12 (SEN4), U23.13 (DRAIN4), U23.18 (KSENSA), U23.19 (SEN2), U23.20 (DRAIN2), U23.22 (AGND), U23.23 (A3); also elsewhere on the board
unnamed: C86.2, J14.7
unnamed: C85.2, D24.1 (K), D25.2 (A), F7.1, J14.10 (V-)
unnamed: F7.2, Q13.5 (D_1), Q13.6 (D_2), Q13.7 (D_3), Q13.8 (D_4), Q13.D1 (D_5), Q13.D2 (D_6), Q13.D3 (D_7), R78.1
unnamed: Q13.4 (G), U23.17 (GATE1)
unnamed: Q13.1 (S_1), Q13.2 (S_2), Q13.3 (S_3), R73.1, R74.1, R75.1, R76.1, R77.1
unnamed: R78.2, U23.16 (DRAIN1)
unnamed: R73.2, U23.15 (SEN1)
unnamed: C83.1, U23.1 (VDD), U23.2 (~RESET), U23.24 (~SHTDWN)
